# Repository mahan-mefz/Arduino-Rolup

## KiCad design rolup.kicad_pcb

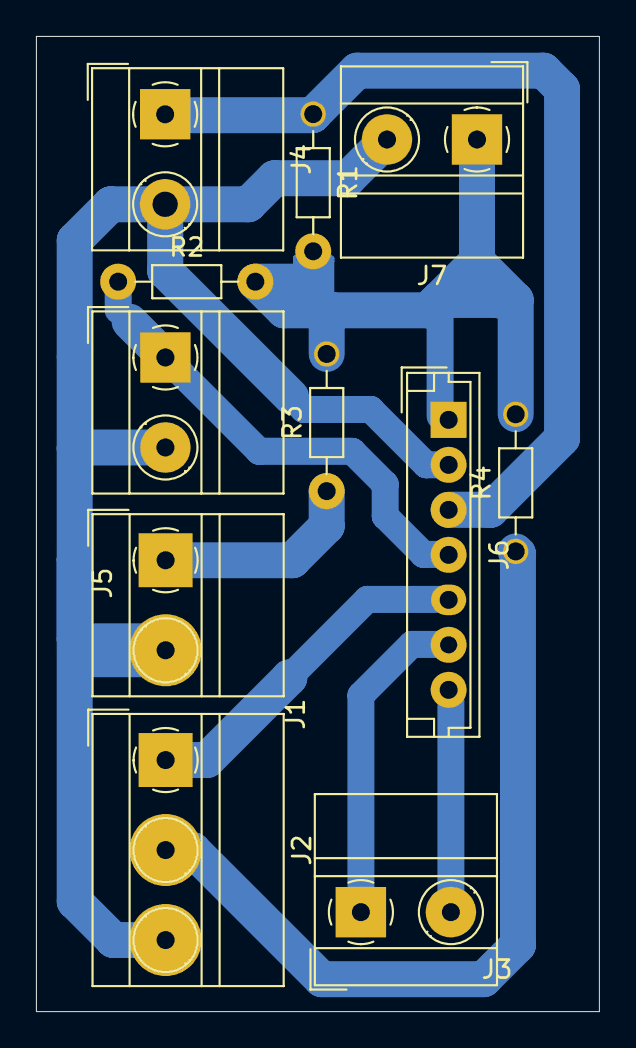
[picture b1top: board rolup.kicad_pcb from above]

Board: 2 copper layers, 31.3 x 54.2 mm, 11 parts (0 on the bottom side), 9 nets.

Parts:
J1: switch; TerminalBlock_MetzConnect_Type011_RT05502HBWC_1x02_P5.00mm_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
J2: Screw_Terminal_01x03; TerminalBlock_MetzConnect_Type011_RT05503HBWC_1x03_P5.00mm_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
J3: bala paiin; TerminalBlock_MetzConnect_Type011_RT05502HBWC_1x02_P5.00mm_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
J4: k a; TerminalBlock_MetzConnect_Type011_RT05502HBWC_1x02_P5.00mm_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
J5: k b; TerminalBlock_MetzConnect_Type011_RT05502HBWC_1x02_P5.00mm_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
J6: Conn_01x07_Pin; JST_EH_B7B-EH-A_1x07_P2.50mm_Vertical
J7: 5+; TerminalBlock_MetzConnect_Type011_RT05502HBWC_1x02_P5.00mm_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
R1, R2, R3, R4: 10 k; R_Axial_DIN0204_L3.6mm_D1.6mm_P7.62mm_Horizontal

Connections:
+5C: J6.1, J7.1, R1.2, R2.2, R3.2, R4.2
GND: J1.2, J2.3, J4.2, J5.2, J6.2, J7.2
unnamed: J1.1, R3.1
unnamed: J2.1, J6.5
unnamed: J2.2, R4.1
unnamed: J3.1, J6.6
unnamed: J3.1 (Pin_2), J6.7
unnamed: J4.1, J6.3, R1.1
unnamed: J5.1, J6.4, R2.1

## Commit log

2024-09-08 فایل اردوینو با استفاده از افزنه vscod ران شد
2024-09-08 پروژه درحال نوشتن است
2024-09-18 کد جدید نوشته با کنترل مجزا
2024-09-18 Revert "کد جدید نوشته با کنترل مجزا"
2024-09-18 فایل برنامه نویس پاک شد
2024-09-18 فایل کمکی در کنار فایل اصلی قرار گرفت
2024-09-23 edit btn
2024-09-25 pcb file
2024-09-25 add save
2024-09-26 pcb rol
2024-09-26 pcd pdf
2024-09-26 pcb file pdf
2024-09-26 file pcb add
2024-09-28 redme
2024-09-28 add ardi
2024-10-05 backups
2024-10-10 file add
2024-10-11 tag ha
